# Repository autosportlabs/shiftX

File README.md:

shiftX
======

A 3 stage sequential shift light designed to integrate with RaceCapture/Pro.

It features a compact size (0.5"x4.95") that can be affixed to a flat surface like a dashboard

See the LICENSE.txt for information on the technology license

Autosport Labs
http://www.autosportlabs.com

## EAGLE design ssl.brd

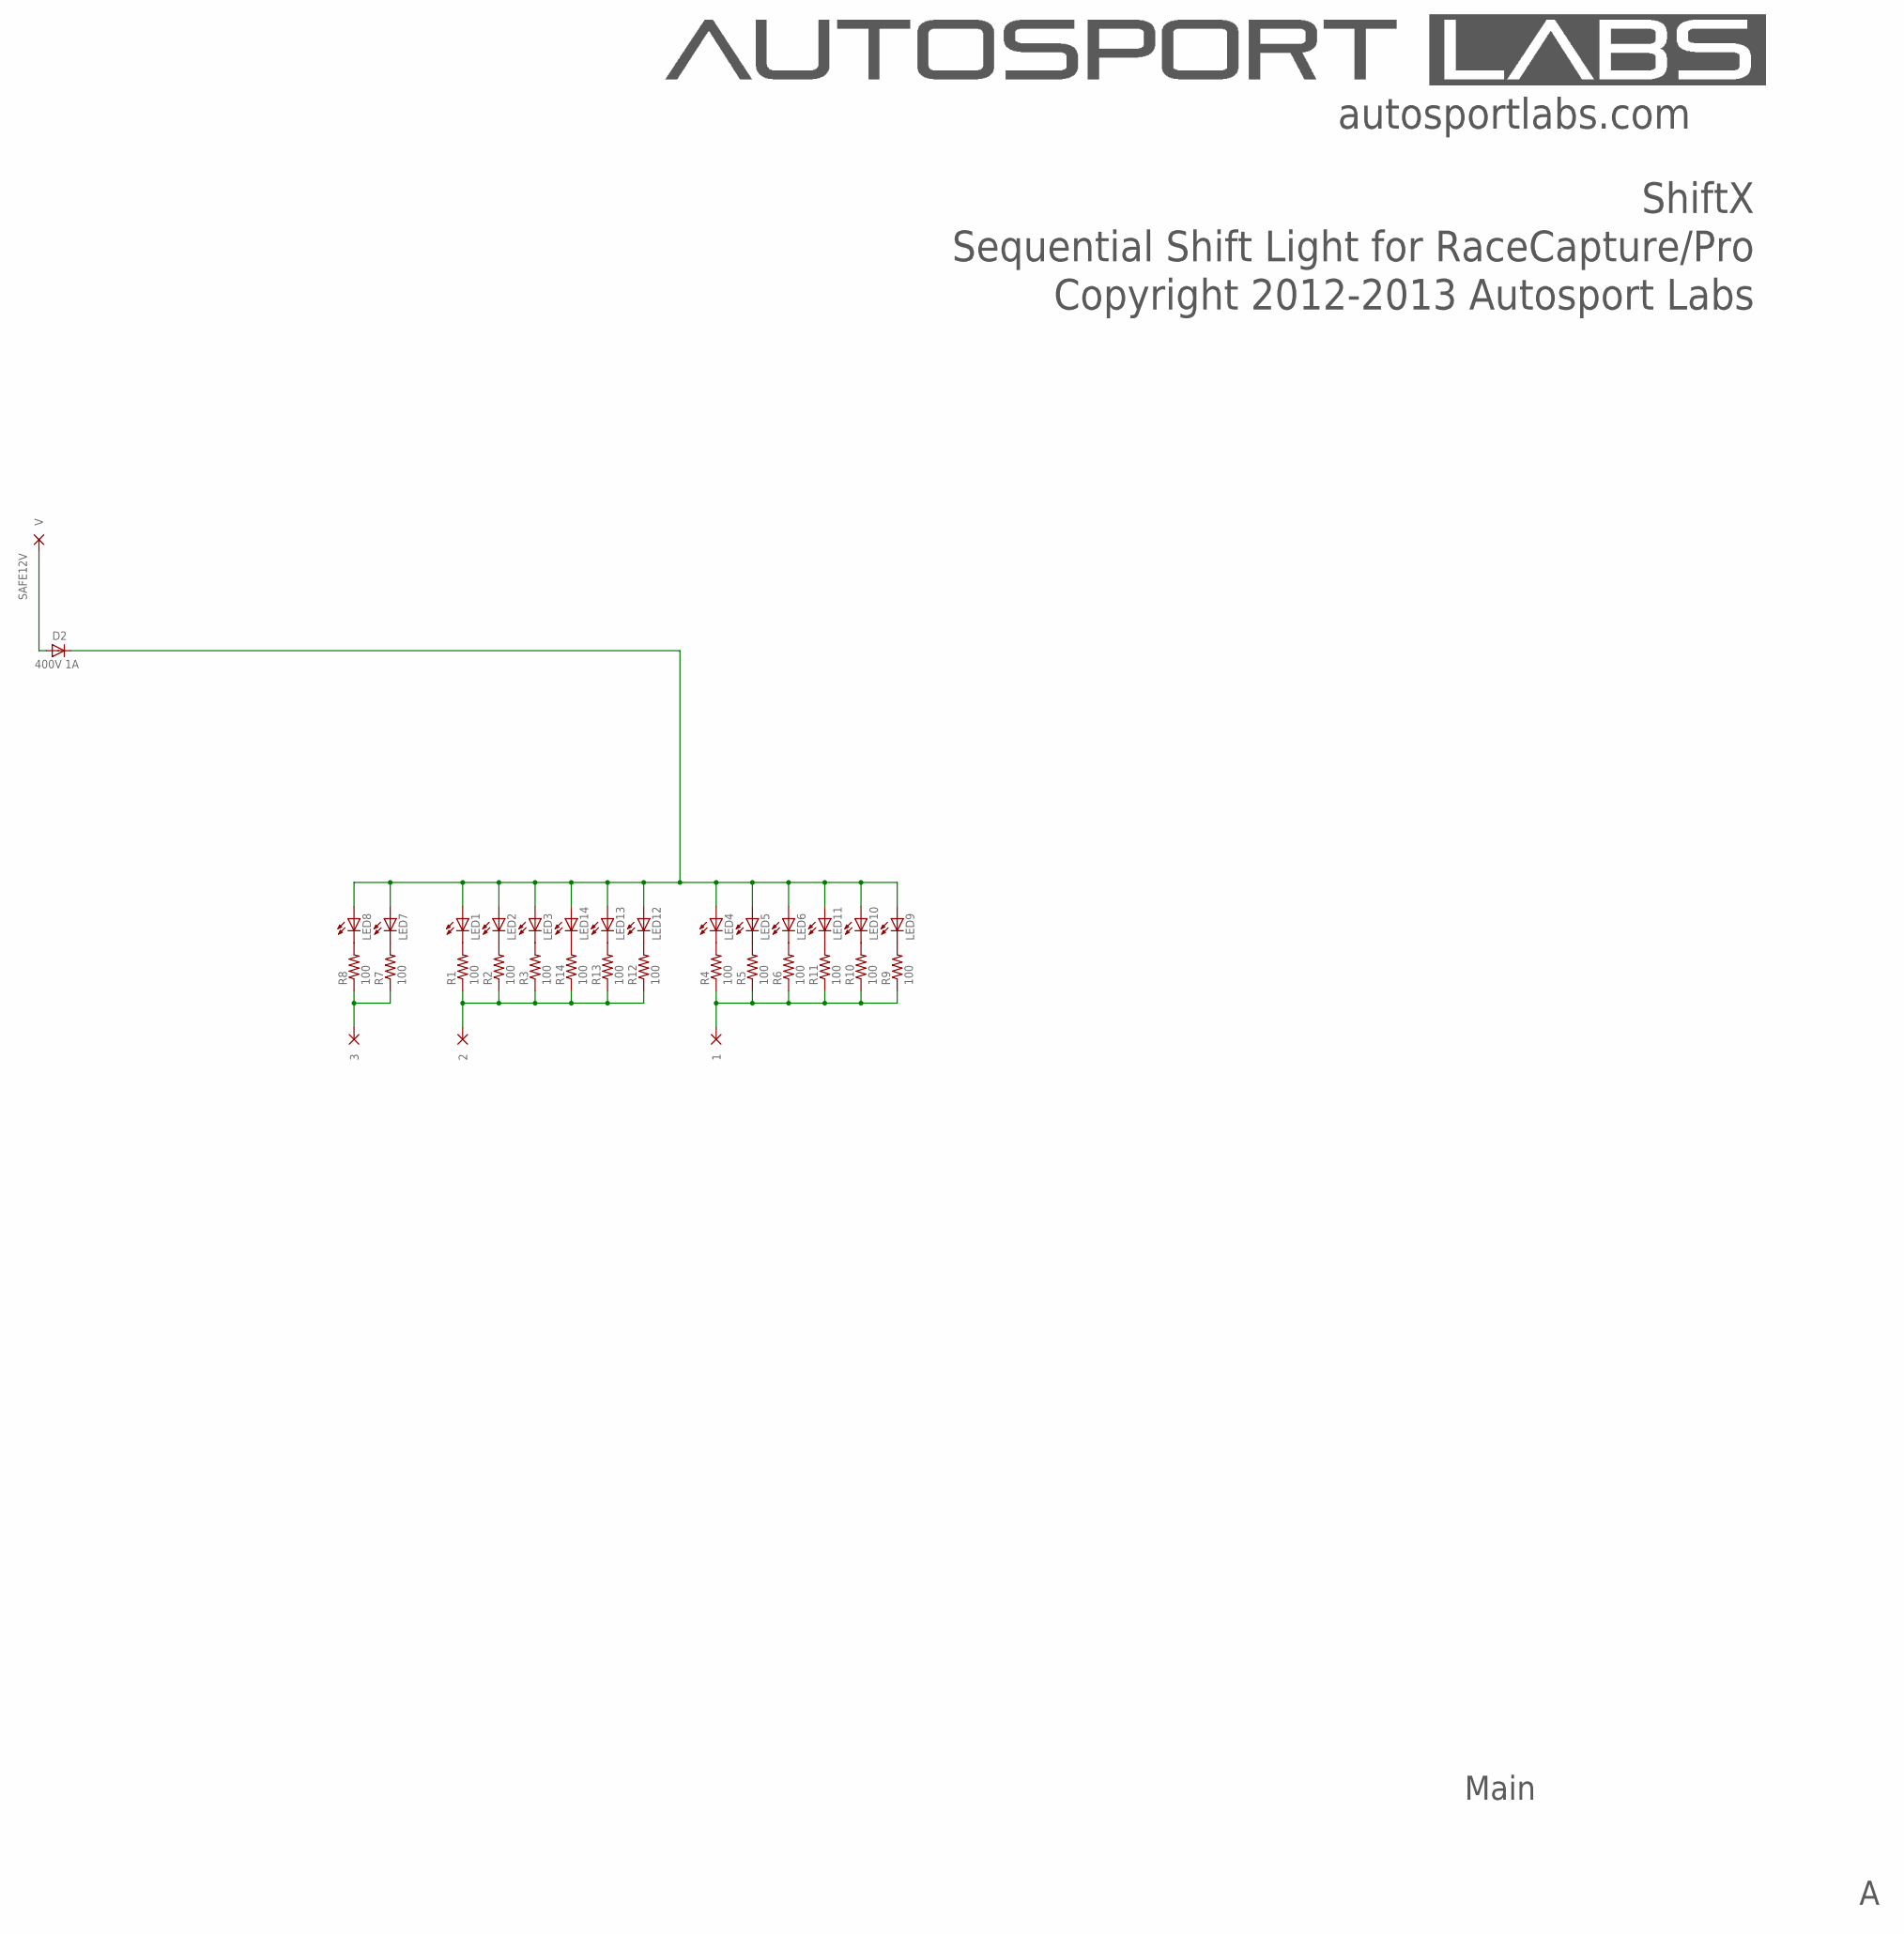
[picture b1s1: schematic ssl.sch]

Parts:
1, 2, 3: WIREPAD2,15/1,0; 2,15/1,0
D2: 400V 1A; SMA
LED1, LED2, LED3, LED4, LED5, LED6, LED7, LED8, LED9, LED10, LED11, LED12, LED13, LED14: LEDP-LCC-2; P-LCC-2
R1, R2, R3, R4, R5, R6, R7, R8, R9, R10, R11, R12, R13, R14: 100; R0603
V: WIREPAD2,15/1,0; 2,15/1,0

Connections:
unnamed: LED8.C, R8.2
unnamed: LED7.C, R7.2
unnamed: LED1.C, R1.2
unnamed: LED2.C, R2.2
unnamed: LED3.C, R3.2
unnamed: LED14.C, R14.2
unnamed: LED13.C, R13.2
unnamed: LED12.C, R12.2
unnamed: LED4.C, R4.2
unnamed: LED5.C, R5.2
unnamed: LED6.C, R6.2
unnamed: LED11.C, R11.2
unnamed: LED10.C, R10.2
unnamed: LED9.C, R9.2
unnamed: 3.1, R7.1, R8.1
unnamed: 2.1, R1.1, R2.1, R3.1, R12.1, R13.1, R14.1
unnamed: 1.1, R4.1, R5.1, R6.1, R9.1, R10.1, R11.1
unnamed: D2.C, LED1.A, LED2.A, LED3.A, LED4.A, LED5.A, LED6.A, LED7.A, LED8.A, LED9.A, LED10.A, LED11.A, LED12.A, LED13.A, LED14.A
SAFE12V: D2.A, V.1

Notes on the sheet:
Copyright 2012-2013 Autosport Labs
ShiftX
autosportlabs.com
Sequential Shift Light for RaceCapture/Pro
Main

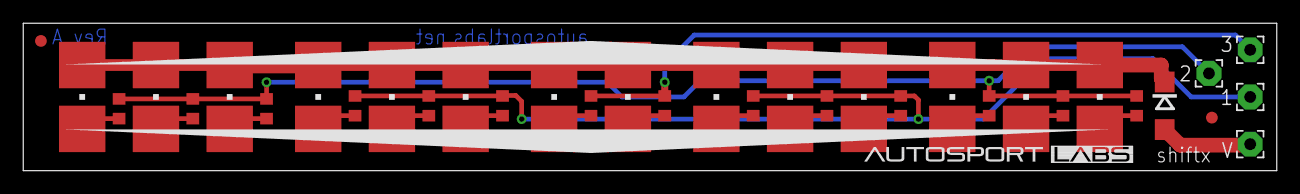
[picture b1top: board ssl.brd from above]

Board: 2 copper layers, 108.0 x 12.7 mm, 33 parts (0 on the bottom side), 19 nets.

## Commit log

2013-01-04 initial cut of sequential shift light
2013-01-28 Rev A of shiftX sequential shift light for Race Capture Pro
2013-01-28 files for RevA release
2013-01-31 grammatical fixes to readme
2013-02-01 re-organizing and adding screenshots
2013-02-01 trying correct board image
2013-10-30 simplified shiftX board
2013-10-30 updated formatting
